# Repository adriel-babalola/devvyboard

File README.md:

## What is it ?
The rp2040 dev board is  a micro-controller unit that consist of the rp2040 micro processor, the 16Mbit SPI NOR Flash, a crystal oscillator that synchronizes communication in the board between the USB abd rp2040, a voltage regulator, reset and boot switch.

##  Why i built it ?
I built devvy, to understand in depth what exactly goes on in a micro-controller, and how exactly do teh components interact, and now i understand what goes on behind the scenes plus i made a rp2040 dev board.

## Assembly Instructions
1. PCB Assembly: All 0402/0603 SMD components soldered by PCBWay PCBA
2. Manual Soldering: 
   - pin Headers 
3. Testing: Apply 5V via USB-C, probe 3V3 rail with multimeter (should show 3.3V), but I tested it with an LED on the 3v3 and it works fine, will proceed to much complex projects later on.
4. Firmware: Flash using RP2040 USB bootloader (hold BOOT, press RESET, drag `.uf2` to `RPI-RP2` drive)

## CAD & Design Files
- PCB Design : KiCAD – see `devvyboard/` folder
- Gerbers: `devvyboard_gebers.zip`
- 3D CAD: `.step` files in `devvyboard_3d_step/` folder

## The Final Soldered Borad

## The CAD View 

## The Schematics 

## The Final Routed PCB

## Bill of Materials

| Name | Purpose | Qty | Total (USD) | Link | Distributor |
|------|---------|-----|-------------|------|-------------|
|Connectors | For external connections | 10 | $1.5 | [Connectors](https://www.aliexpress.com/item/1005007385580884.html?spm=a2g0o.cart.0.0.79ee38dam50Q6e&mp=1&pdp_npi=6%40dis%21USD%21USD+1.49%21USD+1.49%21%21USD+1.49%21%21%21%40211b813f17779407648131433e0a86%2112000040529096976%21ct%21NG%216441071228%21%211%210%21) | Aliexpress
|Soldering Iron | To Solder | 1 | $5.3 | [Soldering Iron](https://www.aliexpress.com/item/1005009943749655.html?spm=a2g0o.cart.0.0.79ee38dam50Q6e&mp=1&pdp_npi=6%40dis%21USD%21USD%2019.66%21USD%205.24%21%21USD%205.24%21%21%21%40211b813f17779407648131433e0a86%2112000050645810711%21ct%21NG%216441071228%21%211%210%21) | Aliexpress
| RP2040 | Dual-core ARM Cortex-M0+ microcontroller — the brain of the board | 1 | $0.69 | [LCSC C2040](https://www.lcsc.com/product-detail/C2040.html) | JLCPCB |
| W25Q16JVUXIQ Flash | 16Mbit SPI NOR Flash — stores firmware and data | 1 | $0.18 | [LCSC C2843335](https://www.lcsc.com/product-detail/C2843335.html) | JLCPCB |
| 12MHz Crystal (X322512MSB4SI) | Crystal oscillator — synchronises USB and RP2040 communication | 1 | $0.04 | [LCSC C9002](https://www.lcsc.com/product-detail/C9002.html) | JLCPCB |
| TYPE-C-31-M-12 USB-C Receptacle | USB-C port — data transfer and board power input | 1 | $0.09 | [LCSC C165948](https://www.lcsc.com/product-detail/C165948.html) | JLCPCB |
| MCP1700T-3302E/TT LDO | 3.3V voltage regulator — powers all 3.3V components | 1 | $0.18 | [LCSC C39051](https://www.lcsc.com/product-detail/C39051.html) | JLCPCB |
| Alps SKRKAHE020 Tactile Switch | Reset/boot switch — resets or boot-selects the RP2040 | 1 | $0.08 | [LCSC C202388](https://www.lcsc.com/product-detail/C202388.html) | LCSC |
| 100nF 0402 Capacitor x11 | Decoupling — filters noise on power rails | 11 | $0.02 | [LCSC C1525](https://www.lcsc.com/product-detail/C1525.html) | JLCPCB |
| 1uF 0402 Capacitor x2 | Bulk decoupling — stabilises power at RP2040 and USB | 2 | $0.02 | [LCSC C52923](https://www.lcsc.com/product-detail/C52923.html) | JLCPCB |
| 10uF 0603 Capacitor x2 | Input/output bulk capacitance — LDO stability | 2 | $0.02 | [LCSC C19702](https://www.lcsc.com/product-detail/C19702.html) | JLCPCB |
| 33pF 0402 Capacitor x2 | Crystal load capacitors — correct oscillator loading | 2 | $0.01 | [LCSC C1557](https://www.lcsc.com/product-detail/C1557.html) | JLCPCB |
| 5.1k 0402 Resistor x2 | USB-C CC resistors — identifies board as USB device to host | 2 | $0.01 | [LCSC C25905](https://www.lcsc.com/product-detail/C25905.html) | JLCPCB |
| 27R 0402 Resistor x2 | USB D+/D- series resistors — USB signal integrity | 2 | $0.01 | [LCSC C352446](https://www.lcsc.com/product-detail/C352446.html) | JLCPCB |
| 1k 0402 Resistor x2 | Current limiting / pull resistors | 2 | $0.01 | [LCSC C11702](https://www.lcsc.com/product-detail/C11702.html) | JLCPCB |
| 10k 0402 Resistor | Pull-up/pull-down bias resistor | 1 | $0.01 | [LCSC C25744](https://www.lcsc.com/product-detail/C25744.html) | JLCPCB |
| PCB Fabrication (devvyboard_Y4) | 2-layer PCB — the board itself | 5 | $2.00 | — | JLCPCB |
| PCBA SMT Assembly | SMT assembly of all SMD components | 2 | $80.06 | — | JLCPCB |
| Shipping PCB | Economical Global Direct Line 14-19 business days | - | $13.10 | — | JLCPCB |
|Shipping Aliexpress | - | - | $5.23 | - | Aliexpress
| **TOTAL** | | | **$107.36** | | |

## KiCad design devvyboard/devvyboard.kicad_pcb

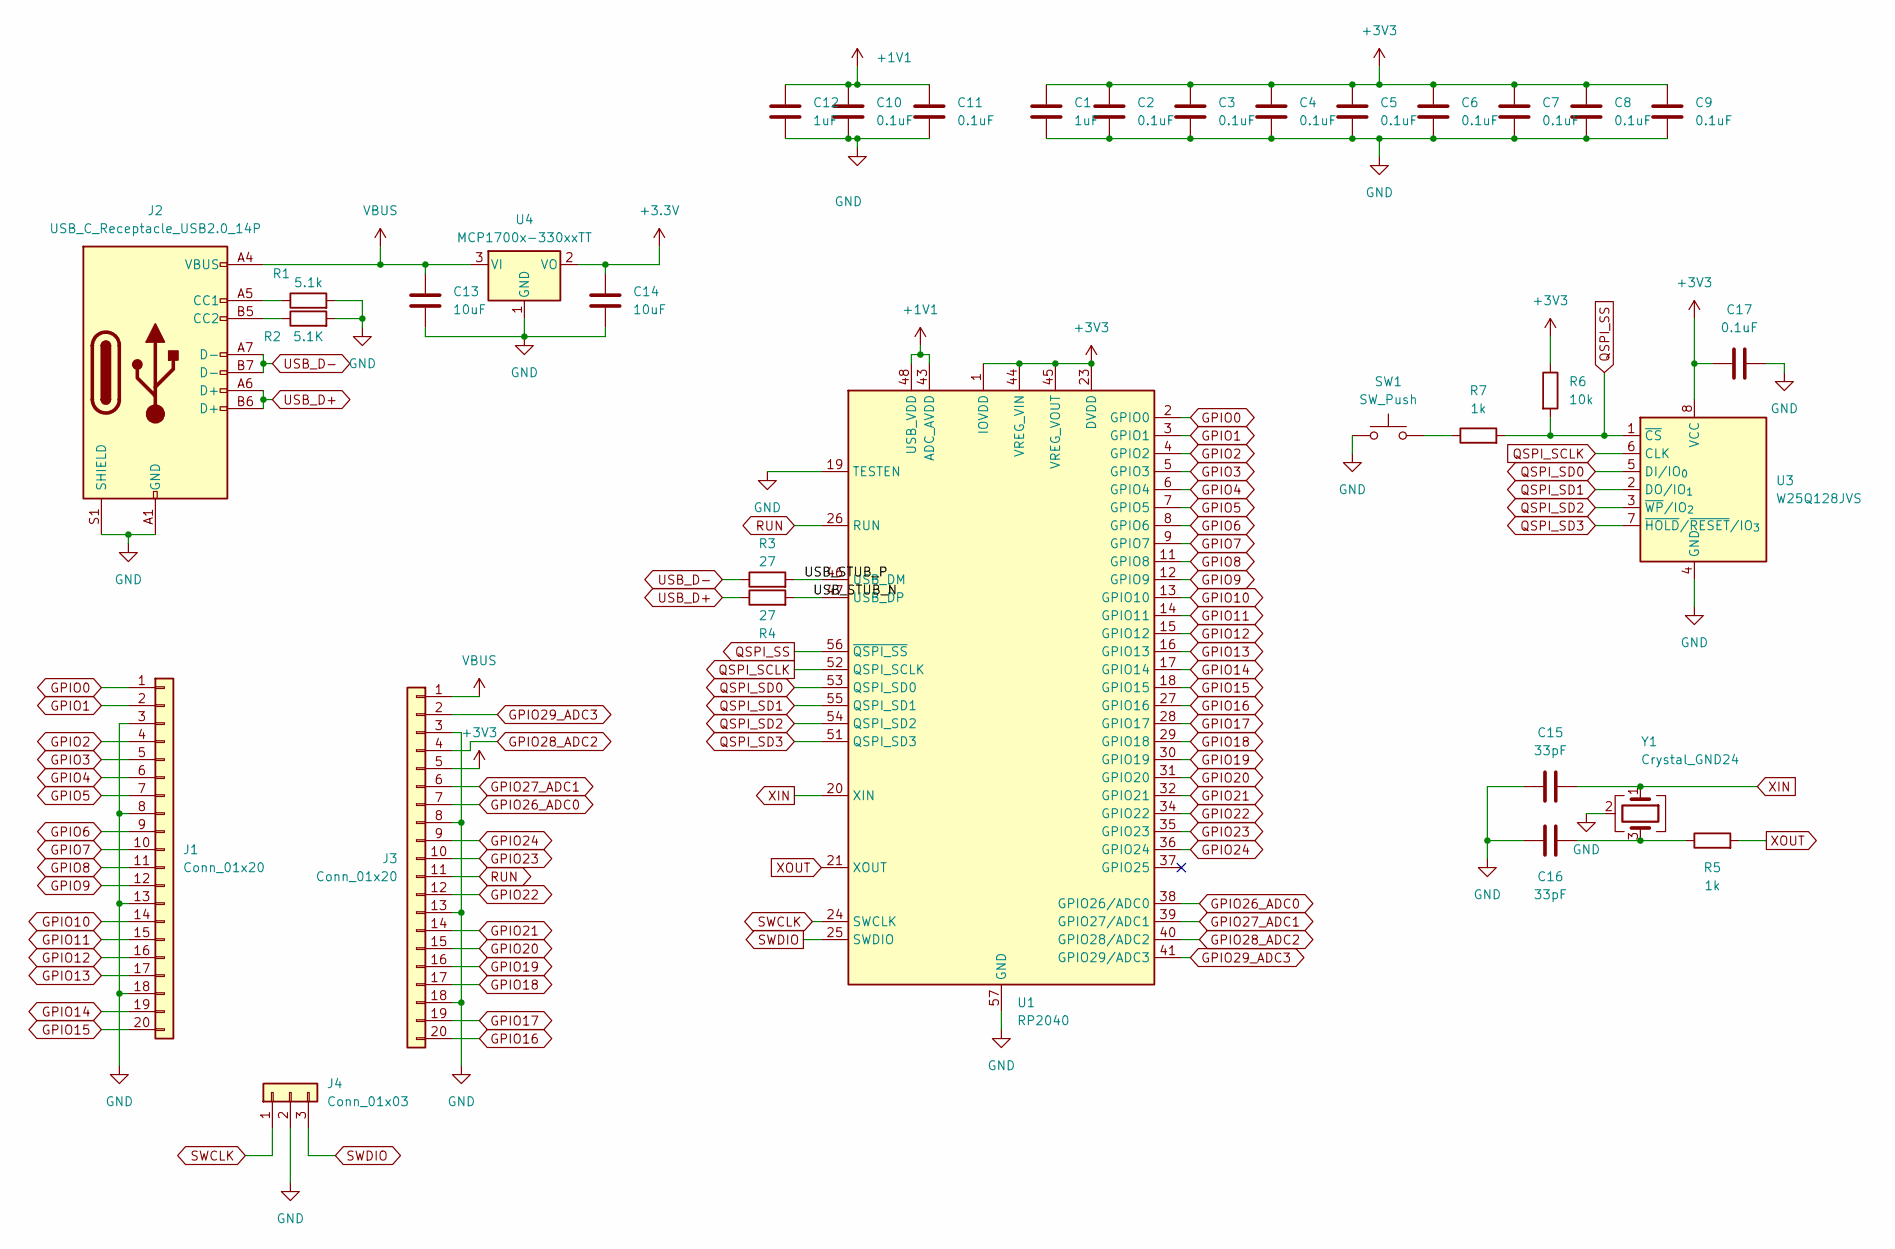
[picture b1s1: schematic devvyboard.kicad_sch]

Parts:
C1, C12: 1uF; C_0402_1005Metric
C2, C3, C4, C5, C6, C7, C8, C9, C10, C11, C17: 0.1uF; C_0402_1005Metric
C13, C14: 10uF; C_0603_1608Metric
C15, C16: 33pF; C_0402_1005Metric
J1, J3: Conn_01x20; PinHeader_1x20_P2.54mm_Vertical
J2: USB_C_Receptacle_USB2.0_14P; USB_C_Receptacle_HRO_TYPE-C-31-M-12
J4: Conn_01x03; PinHeader_1x03_P2.54mm_Vertical
R1: 5.1k; R_0402_1005Metric
R2: 5.1K; R_0402_1005Metric
R3, R4: 27; R_0402_1005Metric
R5, R7: 1k; R_0402_1005Metric
R6: 10k; R_0402_1005Metric
SW1: SW_Push; SW_Push_SPST_NO_Alps_SKRK
U1: RP2040; QFN-56-1EP_7x7mm_P0.4mm_EP3.2x3.2mm
U3: W25Q128JVS; Winbond_USON-8-1EP_3x2mm_P0.5mm_EP0.2x1.6mm
U4: MCP1700x-330xxTT; SOT-23
Y1: Crystal_GND24; Crystal_SMD_3225-4Pin_3.2x2.5mm

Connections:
+1V1: C10.1, C11.1, C12.1, U1.43 (ADC_AVDD), U1.48 (USB_VDD)
/USB_STUB_N: R4.2, U1.47 (USB_DP)
/USB_STUB_P: R3.2, U1.46 (USB_DM)
GND: C1.2, C2.2, C3.2, C4.2, C5.2, C6.2, C7.2, C8.2, C9.2, C10.2, C11.2, C12.2, C13.2, C14.2, C15.1, C16.1, C17.1, J1.3, J1.8, J1.13, J1.18, J2.A1 (GND), J2.A12 (GND), J2.B1 (GND), J2.B12 (GND), J2.S1 (SHIELD), J3.3, J3.8, J3.13, J3.18, J4.2, R1.2, R2.2, SW1.1, U1.19 (TESTEN), U1.57 (GND), U3.4 (GND), U4.1 (GND), Y1.2 (G), Y1.4 (G)
GPIO0: J1.1, U1.2 (GPIO0)
GPIO1: J1.2, U1.3 (GPIO1)
GPIO2: J1.4, U1.4 (GPIO2)
GPIO3: J1.5, U1.5 (GPIO3)
GPIO4: J1.6, U1.6 (GPIO4)
GPIO5: J1.7, U1.7 (GPIO5)
GPIO6: J1.9, U1.8 (GPIO6)
GPIO7: J1.10, U1.9 (GPIO7)
GPIO8: J1.11, U1.11 (GPIO8)
GPIO9: J1.12, U1.12 (GPIO9)
GPIO10: J1.14, U1.13 (GPIO10)
GPIO11: J1.15, U1.14 (GPIO11)
GPIO12: J1.16, U1.15 (GPIO12)
GPIO13: J1.17, U1.16 (GPIO13)
GPIO14: J1.19, U1.17 (GPIO14)
GPIO15: J1.20, U1.18 (GPIO15)
GPIO16: J3.20, U1.27 (GPIO16)
GPIO17: J3.19, U1.28 (GPIO17)
GPIO18: J3.17, U1.29 (GPIO18)
GPIO19: J3.16, U1.30 (GPIO19)
GPIO20: J3.15, U1.31 (GPIO20)
GPIO21: J3.14, U1.32 (GPIO21)
GPIO22: J3.12, U1.34 (GPIO22)
GPIO23: J3.10, U1.35 (GPIO23)
GPIO24: J3.9, U1.36 (GPIO24)
GPIO26_ADC0: J3.7, U1.38 (GPIO26/ADC0)
GPIO27_ADC1: J3.6, U1.39 (GPIO27/ADC1)
GPIO28_ADC2: J3.4, U1.40 (GPIO28/ADC2)
GPIO29_ADC3: J3.2, U1.41 (GPIO29/ADC3)
unnamed: C16.2, R5.1, Y1.3
unnamed: J2.A5 (CC1), R1.1
unnamed: J2.B5 (CC2), R2.1
unnamed: R7.1, SW1.2
QSPI_SCLK: U1.52 (QSPI_SCLK), U3.6 (CLK)
QSPI_SD0: U1.53 (QSPI_SD0), U3.5 (DI/IO_{0})
QSPI_SD1: U1.55 (QSPI_SD1), U3.2 (DO/IO_{1})
QSPI_SD2: U1.54 (QSPI_SD2), U3.3 (~WP/IO_{2})
QSPI_SD3: U1.51 (QSPI_SD3), U3.7 (~HOLD/~RESET/IO_{3})
QSPI_SS: R6.2, R7.2, U1.56 (~QSPI_SS), U3.1 (~CS)
RUN: J3.11, U1.26 (RUN)
SWCLK: J4.1, U1.24 (SWCLK)
SWDIO: J4.3, U1.25 (SWDIO)
USB_D+: J2.A6 (D+), J2.B6 (D+), R4.1
USB_D-: J2.A7 (D-), J2.B7 (D-), R3.1
VBUS: C13.1, J2.A4 (VBUS), J2.A9 (VBUS), J2.B4 (VBUS), J2.B9 (VBUS), J3.1, U4.3 (VI)
XIN: C15.2, U1.20 (XIN), Y1.1
XOUT: R5.2, U1.21 (XOUT)

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
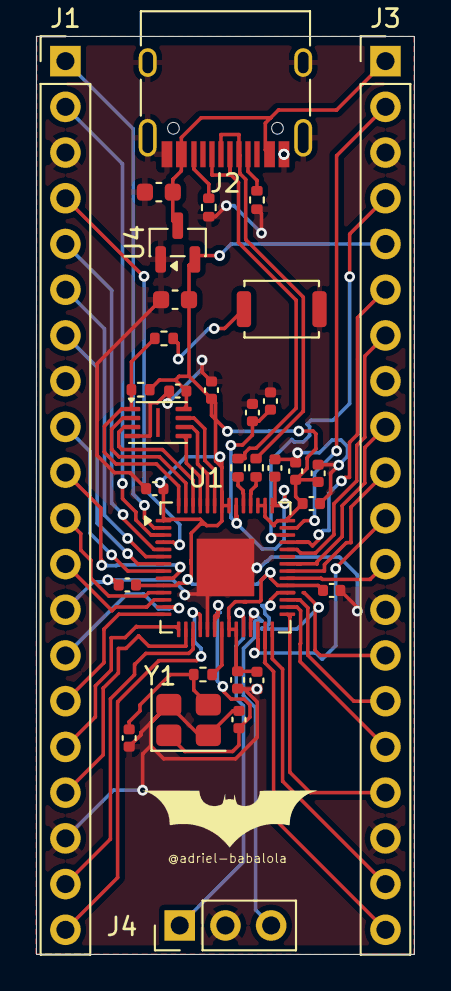
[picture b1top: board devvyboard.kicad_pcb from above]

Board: 2 copper layers, 21.0 x 51.0 mm, 33 parts (0 on the bottom side), 52 nets.

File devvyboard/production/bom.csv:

Designator,Footprint,Quantity,Value,LCSC Part #
"C1, C12",0402,2,1uF,
"C10, C11, C17, C2, C3, C4, C5, C6, C7, C8, C9",0402,11,0.1uF,
"C13, C14",0603,2,10uF,
"C15, C16",0402,2,33pF,
"J1, J3",PinHeader_1x20_P2.54mm_Vertical,2,Conn_01x20,
J2,USB_C_Receptacle_HRO_TYPE-C-31-M-12,1,USB_C_Receptacle_USB2.0_14P,
J4,PinHeader_1x03_P2.54mm_Vertical,1,Conn_01x03,
"R1, R2",0402,2,5.1k,
"R3, R4",0402,2,27,
"R5, R7",0402,2,1k,
R6,0402,1,10k,
SW1,SW_Push_SPST_NO_Alps_SKRK,1,SW_Push,
U1,QFN-56-1EP_7x7mm_P0.4mm_EP3.2x3.2mm,1,RP2040,
U3,Winbond_USON-8-1EP_3x2mm_P0.5mm_EP0.2x1.6mm,1,W25Q16JVUXIQ,
U4,SOT-23,1,MCP1700x-330xxTT,
Y1,Crystal_SMD_3225-4Pin_3.2x2.5mm,1,Crystal_GND24,

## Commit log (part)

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2026-05-04 ready
2026-05-05 proper readme and structure
